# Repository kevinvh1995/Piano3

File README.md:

# VHDL Piano Project

This project involves designing and implementing a functional digital piano on a Terasic DE10-Lite FPGA board using VHDL. The piano will read key presses from a PS/2 keyboard, generate corresponding musical tones, and display information on 7-segment displays. The design follows a modular, structural VHDL approach.

## Project Setup

* **Hardware:** Terasic DE10-Lite Board
* **Software:** Intel Quartus Prime Lite Edition
* **Language:** VHDL-2008
* **Target OS:** Windows
* **Shell:** powershell.exe

### Setup Steps

1. Ensure Intel Quartus Prime is installed.
2. Connect the DE10-Lite board to the PC via USB.
3. Connect a PS/2 keyboard to the GPIO pins using the appropriate interface shield.
4. Open the Quartus project file (`.qpf`) for the current assignment.
5. Compile the VHDL code and program the FPGA.

## Repository Structure Analysis

The repository contains a complete VHDL piano implementation with the following structure:

### Assignment Directories

* **assignment_0**: 7-segment decoder (`seg7dec`) - foundational component

* **assignment_1**: PS/2 serial-to-parallel converter (`showkey`)
* **assignment_2_constantKey**: Key state FSM (`constantkey`)
* **assignment_2_readKey**: Complete keyboard interface (`readkey`)
* **assignment_3**: Clock generator with octave control (`clock_generator`)
* **assignment_4**: Key-to-frequency mapping (`key2pulselength`)
* **assignment_5**: Audio tone generator (`pulselength2audio`)
* **assignment_6**: Integrated tone generation (`tone_generation`)
* **assignment_7**: Top-level piano integration (`piano`)

### Documentation

* **docs/assignment_2_211.md**: Latest assignment specification (v211)

* **docs/requirements.md**: Detailed grading criteria and requirements
* **docs/Course_manual_summary.md**: Complete course overview
* **docs/lesson_summary/**: Weekly lesson notes covering VHDL concepts
* **docs/pedroni_circuit_design/**: Reference material from textbook

### Hardware

* **hardware/**: PS/2 keyboard shield design files (Eagle & KiCad)

* **hardware/images/**: Shield photos and board layouts

## Progress Tracker

### To-Do

#### Phase 1: Component Verification & Testing

* [ ] **Assignment 0 - seg7dec Verification**
  * [ ] Open Quartus project `assignment_0/seg7dec.qpf`
  * [ ] Compile and verify synthesis without errors/warnings
  * [ ] Test all 16 input combinations (0x0-0xF) using waveform simulation
  * [ ] Verify common anode logic (0=on, 1=off) for all segments
  * [ ] Document any issues and validate against truth table
  * [ ] Test on hardware with switches if available

* [ ] **Assignment 1 - showkey Verification**
  * [ ] Open Quartus project `assignment_1/showkey.qpf`
  * [ ] Analyze PS/2 protocol implementation in `showkey.vhd`
  * [ ] Compile and resolve any synthesis issues
  * [ ] Run testbench `showkey_tb.vhd` in ModelSim
  * [ ] Verify 11-bit frame parsing (start, 8 data, parity, stop)
  * [ ] Test byte_read signal timing and scancode output
  * [ ] Validate falling edge detection of kbclock
  * [ ] Document bit counter logic and frame assembly

* [ ] **Assignment 2a - constantkey FSM Verification**
  * [ ] Open Quartus project `assignment_2_constantKey/constantkey.qpf`
  * [ ] Analyze Moore FSM implementation with 5 states
  * [ ] Verify state transition logic in RTL viewer
  * [ ] Run testbench `constantkey_tb.vhd` in ModelSim
  * [ ] Test key press/release sequence detection
  * [ ] Verify 0xF0 release code handling
  * [ ] Validate memory signals for dig2/dig3 debug outputs
  * [ ] Check for latch inference warnings

* [ ] **Assignment 2b - readkey Integration Verification**
  * [ ] Open Quartus project `assignment_2_readKey/readkey.qpf`
  * [ ] Analyze structural VHDL combining clock_domain_crossing, showkey, constantkey
  * [ ] Verify signal connections in RTL viewer
  * [ ] Run integrated testbench `readkey_tb2.vhd`
  * [ ] Test complete keyboard interface pipeline
  * [ ] Validate clock domain crossing synchronizers
  * [ ] Verify end-to-end key press to scancode output

* [ ] **Assignment 3 - clock_generator Verification**
  * [ ] Open Quartus project `assignment_3/clock_generator.qpf`
  * [ ] Analyze FSM controlling clock divider multiplexer
  * [ ] Verify 7 octave states (50MHz down to 0.78125MHz)
  * [ ] Run testbench `tb_clock_generator.vhd`
  * [ ] Test 'A' key (octave up) and 'Z' key (octave down) responses
  * [ ] Validate frequency division ratios in simulation
  * [ ] Check state machine viewer in Quartus

* [ ] **Assignment 4 - key2pulselength Verification**
  * [ ] Open Quartus project `assignment_4/key2pulselength.qpf`
  * [ ] Analyze lookup table implementation for note frequencies
  * [ ] Verify scancode to frequency divisor mapping
  * [ ] Run testbench `tb_key2pulselength.vhd`
  * [ ] Test key mappings from Table 3 (22 notes)
  * [ ] Validate integer range 0-8191 for pulselength output
  * [ ] Cross-reference with musical note frequencies

* [ ] **Assignment 5 - pulselength2audio Verification**
  * [ ] Open Quartus project `assignment_5/pulselength2audio.qpf`
  * [ ] Analyze counter-based frequency divider
  * [ ] Verify audio square wave generation logic
  * [ ] Run testbench `tb_pulselength2audio.vhd`
  * [ ] Test with various pulselength values (0, 100, 1000, 7000)
  * [ ] Measure output frequencies and validate timing
  * [ ] Verify stereo output (audiol, audior)

* [ ] **Assignment 6 - tone_generation Integration**
  * [ ] Open Quartus project `assignment_6/tone_generation.qpf`
  * [ ] Verify structural combination of clock_generator, key2pulselength, pulselength2audio
  * [ ] Run testbench `TB_tone_generation.vhd`
  * [ ] Test complete tone synthesis pipeline
  * [ ] Validate signal connections in RTL viewer
  * [ ] Verify octave shifting affects output frequency correctly

#### Phase 2: System Integration & Hardware Testing

* [ ] **Assignment 7 - Top-Level Piano Integration**
  * [ ] Open Quartus project `assignment_7/piano.qpf`
  * [ ] Analyze top-level structural VHDL connections
  * [ ] Verify pin assignments in `piano.qsf` file
  * [ ] Compile full system and resolve any errors
  * [ ] Run complete system testbench `tb_piano.vhd`
  * [ ] Validate HEX display connections (4x seg7dec instances)
  * [ ] Check Arduino shield pin mappings (io3-io5)

* [ ] **Hardware Preparation**
  * [ ] Verify DE10-Lite board availability and setup
  * [ ] Check PS/2 keyboard shield assembly
  * [ ] Test PS/2 keyboard with shield connection
  * [ ] Verify speaker output on shield
  * [ ] Program FPGA with compiled piano.sof file

* [ ] **System Validation & Testing**
  * [ ] Test reset functionality (KEY1, LED0 indicator)
  * [ ] Verify 7-segment displays show scancode values
  * [ ] Test all mapped piano keys for audio output:
    * [ ] QWERTY row (white keys): Q,W,E,R,T,Y,U,I,O,P
    * [ ] Number row (black keys): 1,2,3,4,5,6,7,8,9,0
  * [ ] Test octave controls:
    * [ ] 'A' key increases octave (higher pitch)
    * [ ] 'Z' key decreases octave (lower pitch)
  * [ ] Validate audio frequencies match expected musical notes
  * [ ] Test key press/release state management
  * [ ] Record demonstration video for submission

#### Phase 3: Code Quality & Documentation

* [ ] **VHDL Code Review & Standards Compliance**
  * [ ] Verify all reserved words use CAPITALS
  * [ ] Check consistent indentation across all files
  * [ ] Validate meaningful signal and variable names
  * [ ] Ensure proper use of CONSTANT declarations
  * [ ] Verify no BUFFER ports are used
  * [ ] Check TYPE definitions for all FSM states
  * [ ] Validate rising_edge(clk) usage over clk'EVENT
  * [ ] Review sensitivity lists for completeness
  * [ ] Check for latch inference warnings

* [ ] **Documentation & Comments Enhancement**
  * [ ] Update file headers with student information
  * [ ] Add comprehensive component documentation
  * [ ] Document all signal purposes and connections
  * [ ] Create architecture diagrams for complex components
  * [ ] Add timing diagrams for critical interfaces
  * [ ] Document design decisions and trade-offs

* [ ] **Testbench Validation & Coverage**
  * [ ] Ensure all components have working testbenches
  * [ ] Validate test coverage for edge cases
  * [ ] Add assertions for automatic verification
  * [ ] Document expected vs actual results
  * [ ] Create waveform screenshots for key tests
  * [ ] Verify ModelSim integration and wave files

#### Phase 4: Final Integration & Submission

* [ ] **Project Packaging & Git Management**
  * [ ] Create clean Git repository with proper structure
  * [ ] Add comprehensive README with setup instructions
  * [ ] Include pin assignment files and constraints
  * [ ] Package hardware test procedures
  * [ ] Create project release with ZIP archive
  * [ ] Validate all files compile without external dependencies

* [ ] **Performance Optimization & Analysis**
  * [ ] Review RTL viewer for optimal hardware utilization
  * [ ] Check timing analysis and slack margins
  * [ ] Optimize critical path delays if needed
  * [ ] Validate resource usage (LUTs, registers, RAM)
  * [ ] Document any performance bottlenecks

* [ ] **Final System Validation**
  * [ ] Perform complete end-to-end system test
  * [ ] Validate all functional requirements
  * [ ] Test edge cases and error conditions
  * [ ] Verify robust operation under various conditions
  * [ ] Create final demonstration video
  * [ ] Prepare oral presentation materials

### In-Progress

* [x] Repository analysis and documentation (COMPLETED)

* [x] Understanding project architecture and dependencies (COMPLETED)
* [x] Technical requirements identification (COMPLETED)
* [ ] Component-by-component verification starting with Assignment 0

### Done

* [x] Complete repository structure analysis

* [x] Documentation review and synthesis of all course materials
* [x] Technical requirements identification and grading criteria understanding
* [x] VHDL code analysis of key components (seg7dec, showkey, constantkey, piano)
* [x] Architecture mapping and component dependency analysis
* [x] README.md comprehensive documentation update
* [x] Progress tracker framework establishment with extensive task breakdown

## Architecture Overview

The VHDL piano consists of two main subsystems:

### 1. Keyboard Interface (`readKey`)

* **Clock Domain Crossing**: Synchronizes PS/2 signals (20kHz) to FPGA clock (50MHz)

* **Serial Decoder (`showkey`)**: Converts 11-bit PS/2 frames to 8-bit scancodes
* **State Machine (`constantkey`)**: Manages key press/release events and hold states

### 2. Tone Generation (`tone_generation`)

* **Clock Generator**: FSM-controlled frequency divider for octave selection

* **Key Mapper**: Lookup table converting scancodes to frequency divisors
* **Audio Generator**: Variable-frequency square wave generator

### 3. User Interface

* **7-Segment Displays**: Debug output showing current/previous key scancodes

* **Audio Output**: Square wave tones through Arduino shield speaker
* **Control**: Reset via KEY1, octave control via 'A'/'Z' keys

## Key Technical Concepts Implemented

### VHDL Design Patterns

* **Structural VHDL**: Hierarchical component instantiation

* **Moore FSMs**: State machines with output dependent only on current state
* **Clock Domain Crossing**: Two-flip-flop synchronizers for metastability prevention
* **Concurrent vs Sequential**: Proper use of processes vs concurrent statements

### Hardware Concepts

* **PS/2 Protocol**: 11-bit serial frames with clock/data handshaking

* **Audio Generation**: Digital frequency synthesis using counters
* **7-Segment Displays**: Common anode display driving with lookup tables

## Design Notes & Rationale

### Architecture Decisions

* All finite state machines use Moore machine architecture for predictable outputs

* Clock domain crossing properly handled with two-flip-flop synchronizers
* Signal naming follows consistent conventions (e.g., `C_` prefix for internal signals)
* Constants used for all magic numbers and configuration values
* Structural VHDL used for clear hierarchical design

### VHDL Best Practices Observed

* **Code Style**: CAPITALS for reserved words, consistent indentation

* **Language Usage**: `CONSTANT`s instead of magic numbers, avoid `BUFFER` ports
* **FSM Implementation**: `TYPE` definitions for state names, proper sensitivity lists
* **Edge Detection**: `rising_edge(clk)` preferred over `clk'EVENT AND clk='1'`
* **Testbenches**: Comprehensive verification for each component

### Frequency Calculation

Musical notes follow the equal temperament scale where each semitone is 2^(1/12) ≈ 1.05946 times the previous.
Base frequency: A4 = 440 Hz
Octave relationship: A5 = 880 Hz (2 × A4)

## Component Dependencies

```
piano (top-level)
├── readkey
│   ├── clock_domain_crossing
│   ├── showkey  
│   └── constantkey
├── tone_generation
│   ├── clock_generator
│   ├── key2pulselength
│   └── pulselength2audio
└── seg7dec (×4 instances)
```

## Key Requirements Summary

### Functional Requirements

* Generate correct musical tones for mapped keys (QWERTY row = white keys, number row = black keys)

* Octave changes with 'A' (up) and 'Z' (down) keys  
* Display current and previous key scancodes on HEX displays
* Reset functionality via KEY1 with LED0 status indication

### Technical Requirements

* **Code Style**: Use CAPITALs for reserved words, consistent indentation, meaningful comments

* **VHDL Usage**: Use `CONSTANT`s, avoid `BUFFER` ports, use `TYPE` for FSM states, use `rising_edge(clk)`
* **Architecture**: Modular structural VHDL design with Moore machine FSMs
* **Verification**: Testbenches for all components, simulation-based validation

### Grading Criteria (70% Code + 30% Oral)

* **Code Style** (20%): Formatting, comments, documentation

* **VHDL Language Usage** (30%): Proper constructs, no latches, good FSM design
* **Functionality** (50%): Working audio, octave control, displays, reset

## Courses

This library is used in the following coures:

* D-H-ESE-SOC

Please contact the lecturer of your course when the course you attend is not mentioned here.

# PS/2 interface shield

The hardware for the [PS/2 interface shield](hardware/README.md) is available.

## Disclaimer

Project templates and materials for the VHDL ALU assignment in SOC class is distributed in the hope that it will be useful, but WITHOUT ANY WARRANTY; Without even the implied warranty of MERCHANTABILITY or FITNESS FOR A PARTICULAR PURPOSE.

## License

VHDL examples for use in SOC class are free: You can redistribute it and/or modify it under the terms of a Creative Commons Attribution-NonCommercial 4.0 International License (<http://creativecommons.org/licenses/by-nc/4.0/>) by Remko Welling (<https://ese.han.nl/~rwelling/>) E-mail: <remko.welling@han.nl>.

<br />This work is licensed under a <a rel="license" href="http://creativecommons.org/licenses/by-nc/4.0/">Creative Commons Attribution-NonCommercial 4.0 International License</a>.

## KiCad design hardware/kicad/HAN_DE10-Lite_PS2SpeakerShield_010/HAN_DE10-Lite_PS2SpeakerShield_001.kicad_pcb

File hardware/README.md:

# PS/2 keyboard interface shield for DE10-Lite
All information required to build your own PS/2 keyboard interface shield for DE10-Lite.

## Responsible disclosure 
Students and lecturers are encouraged to send in their experiences, problems, errors, any other observation while using this document or the PS/2 keyboard interface shield for DE10-Lite. Please send your feedback to one of the lecturers, by raising an issue with this repository, so we can improve this paper. Thank you.

More about responsible disclosure, see: https://en.wikipedia.org/wiki/Responsible_disclosure 

## Disclaimer
The PS/2 keyboard interface shield for DE10-Lite is provided in the hope that it will be useful, but WITHOUT ANY WARRANTY; without even the implied warranty of MERCHANTABILITY or FITNESS FOR A PARTICULAR PURPOSE.
  
## License
The PS/2 keyboard interface shield for DE10-Lite is part of the SOC classes for HAN Engineering Hoofdmodule Embedded Hardware Engineering.

The design of the PS/2 keyboard interface shield for DE10-Lite is free: You may redistribute it and/or modify it under the terms of a Creative  Commons Attribution-NonCommercial 4.0 International License (http://creativecommons.org/licenses/by-nc/4.0/).

<br />This work is licensed under a <a rel="license" href="http://creativecommons.org/licenses/by-nc/4.0/">Creative Commons Attribution-NonCommercial 4.0 International License</a>.

# About this documentation
In the System On Chip Classes of the University of Applied sciences of Arnhem and Nijmegen (HAN) one assignment is used to introduce the students to the use of sequential VHDL code. The assignment is constructing a electronic piano using VHDL on a DE10-Lite FPGA prototype board. 

Where some predecessors of the DE10-lite board were equipped with a PS/2 female connector, the DE10-Lite is equipped with Arduino shield compatible connectors but not the PS/2 connector. This complicates the connection of a PS/2 keyboard to the DE10-Lite significantly. Therefore a interface board was developed that will use the Arduino shield factor connectors and piggy-back on the DE10-Lite board.

[Full size picture of Shield on DE10-Lite board](images/PS2SpeakerShieldOnDE10-Lite_small.png)

# Design
The purpose of the PS/2 keyboard interface shield to add neccessary electronics and make the levelchanges from 5V TTL to the 3,3V domain to guard the FPGA from damage.

The PS/2 keyboard interface shield is designed with reproduction in mind. Component selection was made to allow a introduction to working with SMD components an doldering of those. Therefore 1206 sized components are used in the design to introduce to SMD and regular trough-hole components.

The shield delivers:
 - PS/2 compatible interface to the FPGA on the DE10-Lite board. Any PS/2 compatible keyboard can be connected to the shield.
 - Loudspeaker to make tones of the VHDL-piano audible.
 
### USB-keyboards
As PS/2 is depreciated, modern keyboards have a USB connector. It was out of scope to develop a USB interface for the DE10-Lite board but from experince it was found that simple USB to PS/2 adapters work fine.

## Schematic
The electronics design for the shield is copied from the DE0-CV FPGA board schematics. Follow this link to view or download the [full size schematic](images/PS2SpeakerShield.png)

The [Eagle schematic file ](eagle/HAN_DE10-Lite_PS2SpeakerShield_001.sch) is available for download.

## PCB design
The [Eagle board file ](eagle/HAN_DE10-Lite_PS2SpeakerShield_001.brd) is available for download.

## Component layout
For soldering the component layout is made availabale separately. Click on "[Full size component layout](images/PS2SpeakerShield_BoardTopView.png)" to view or download the component layout. 

# Ordering
For PCB ordering and delivery in Europe, Aisler is recommended: https://aisler.net/ where you can directly order the board following this link: https://aisler.net/p/FWVGCYFB

## BOM
The Bill of Materials (BOM) contains easy obtainable components that can be purchased online:
```
Part Value   Package            Description
C1   100n    C1206              CAPACITOR
C2   100n    C1206              CAPACITOR
C3   100n    C1206              CAPACITOR
C4   100n    C1206              CAPACITOR
D1   BAT54S  SOT23              Schottky barrier (double)
D2   BAT54S  SOT23              Schottky barrier (double)
D3   BAT54S  SOT23              Schottky barrier (double)
D4   BAT54S  SOT23              Schottky barrier (double)
R1   2K      M1206              RESISTOR
R2   2K      M1206              RESISTOR
R3   2K      M1206              RESISTOR
R4   2K      M1206              RESISTOR
R5   200     M1206              RESISTOR
R6   200     M1206              RESISTOR
R7   200     M1206              RESISTOR
R8   200     M1206              RESISTOR
R9   200     M1206              RESISTOR
X1   DIN6FE  M_DIN6             6-PIN MINI-DIN female connector
LS1  SPEAKER PCB_MOUNT_SPEAKER  Speaker
```

# Soldering the PS/2 keyboard shield
Soldering the PS/2 keyboard interface shield kit is fun!

 - For those who start with soldering, Sparkfun hase a nice how-to availabale: https://learn.sparkfun.com/tutorials/how-to-solder-through-hole-soldering/
 - For soldering SMD components the instructions of David Haillant are recommended: http://www.davidhaillant.com/smd-soldering/
 
In this (Dutch) instruction we are soldering SMD 1206 components on the PS/2 keyboard interface PCB.

## Recommended order
When soldering the recommended order is to work "from small to big".

 1. Start with soldering the SMD resisitors
 2. Than solder the SMD capacitors
 3. Finalize soldering SMD components with the diodes
 4. Solder the loadspeaker
 5. Solder the PS/2 connector
 6. Cut the pin-headers to the reqired length
 6. Solder the pin-headers

# Testing

To test the PS/2 keyboard interface shield use the Quartus project that is provided with this repository: [Hardware test for PS/2 interface shield for DE10-Lite](harwareTest/README.md)

# Conclusion
Soldering is fun! I hope you enjoy your self-made PS/2 keyboard interface shield and the joy of playing your VHDL piano.

# Errata
Date      | Issue
----------|-------------
25-3-2021:| Resistors R5 to R9 have been replaced by 200 ohm.

# Hacks
Some hacks are possible to the board:

## Increase speaker audio.
The loudspeaker audio is attennuated using R9. To increase audio volume replace R9 with 0 ohm (bridge).

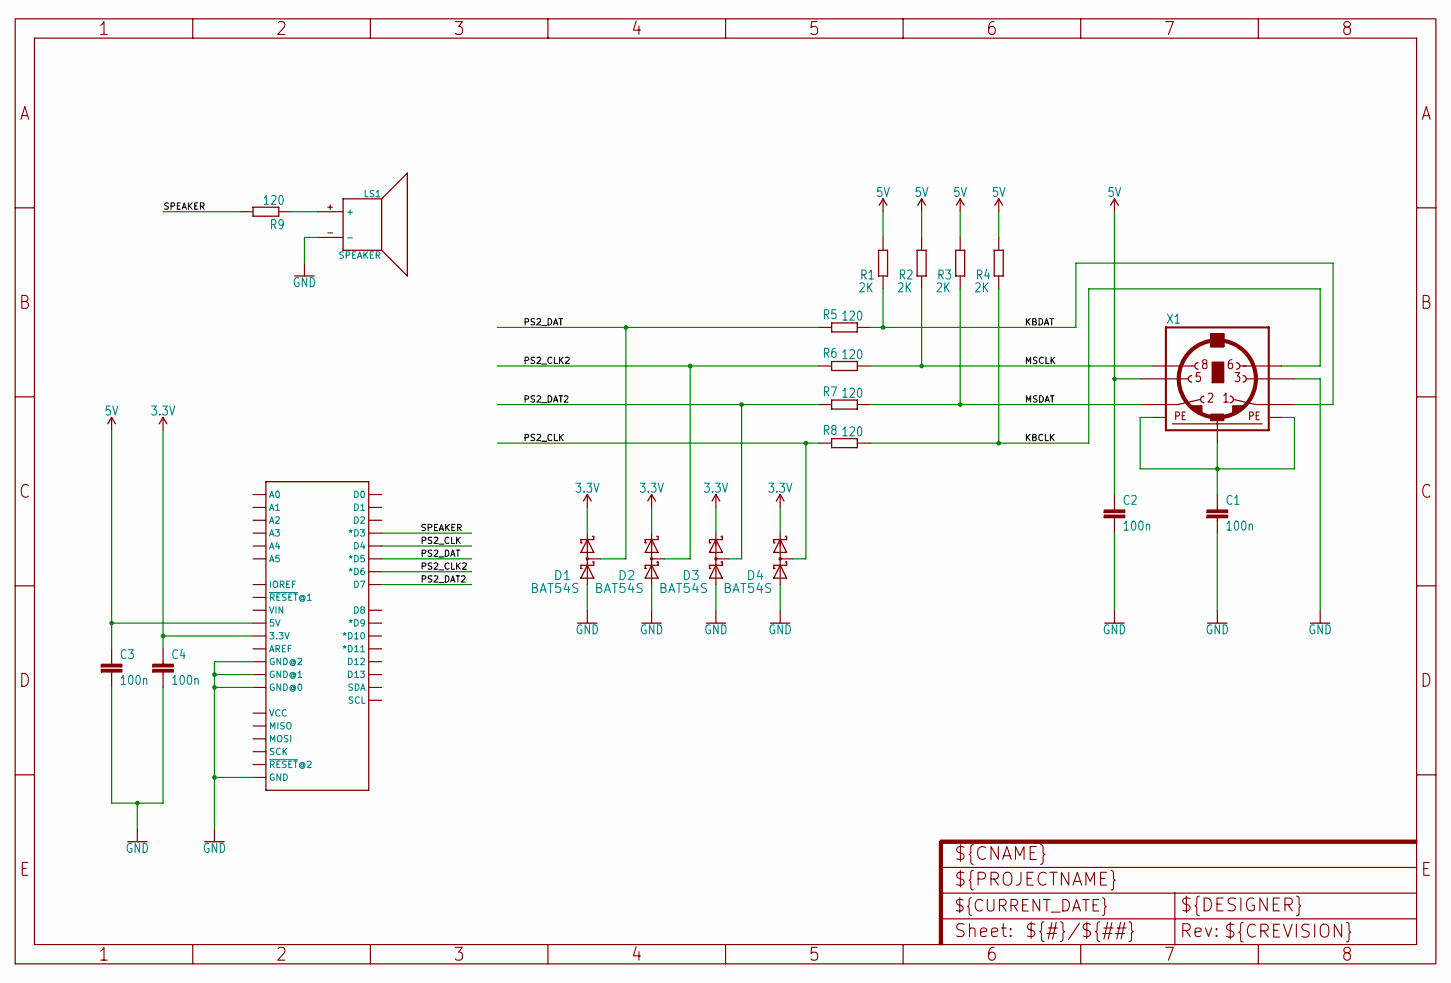
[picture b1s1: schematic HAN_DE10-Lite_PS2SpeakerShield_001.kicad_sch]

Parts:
B1: ARDUINO_UNO_R3_SHIELD_ICSP; UNO_R3_SHIELD_ICSP
C1, C2, C3, C4: 100n; C1206
D1, D2, D3, D4: BAT54S; SOT23
LS1: SPEAKER; PCB_MOUNT_SPEAKER
R1, R2, R3, R4: 2K; M1206
R5, R6, R7, R8, R9: 120; M1206
X1: MINI_DIN_6; M_DIN6

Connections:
3.3V: B1.3.3V, C4.1, D1.2 (K2), D2.2 (K2), D3.2 (K2), D4.2 (K2)
5V: B1.5V, C2.1, C3.1, R1.2, R2.2, R3.2, R4.2, X1.5
GND: B1.GND@0, B1.GND@1, B1.GND@2, B1.GND_ICSP (GND), C1.2, C2.2, C3.2, C4.2, D1.1 (A1), D2.1 (A1), D3.1 (A1), D4.1 (A1), LS1.-, X1.3
KBCLK: R4.1, R8.1, X1.6
KBDAT: R1.1, R5.1, X1.1
MSCLK: R2.1, R6.1, X1.8
MSDAT: R3.1, R7.1, X1.2
unnamed: LS1.+, R9.1
unnamed: C1.1, X1.SH1 (PE1), X1.SH2 (PE2), X1.SH3 (PE3)
PS2_CLK: B1.D4, D4.3 (K1A2), R8.2
PS2_CLK2: B1.D6 (*D6), D2.3 (K1A2), R6.2
PS2_DAT: B1.D5 (*D5), D1.3 (K1A2), R5.2
PS2_DAT2: B1.D7, D3.3 (K1A2), R7.2
SPEAKER: B1.D3 (*D3), R9.2

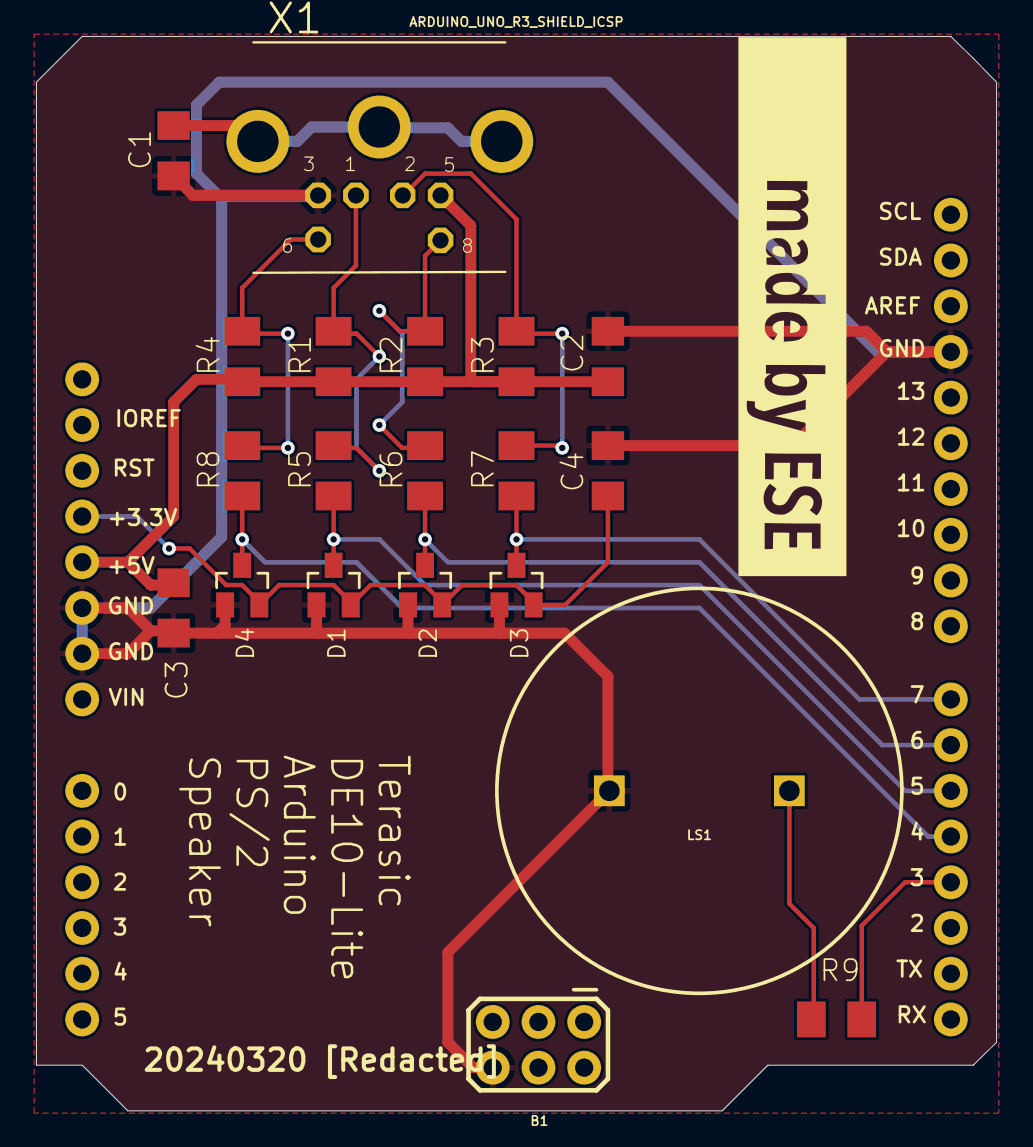
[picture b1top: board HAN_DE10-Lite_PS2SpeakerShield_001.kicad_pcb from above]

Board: 2 copper layers, 53.3 x 59.7 mm, 20 parts (0 on the bottom side), 14 nets.

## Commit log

2020-03-21 Added board an assignment 4
2020-03-22 Added templates for assignments 1 and 2
2020-03-31 Added exercise 0 1 and b
2020-04-01 Added FSM example
2020-04-03 Updated assignment_2, split in to two parts according to manual.
2020-04-06 Added example clock divider
2020-04-07 Added assignment 3 and 4
2020-04-07 Added top-level Entity piano.vhd
2020-04-09 Simplified assignment 0, renamed a to 0 and removed b
2020-05-04 Changed naming states
2020-05-13 Update hardware documentation
2020-05-13 Added readme.md to hardware
2020-05-13 Another update
2020-05-14 Updated shield documentation
2020-05-14 Final addition to hardware/README.md
2020-05-14 Duh, always something you forget
2020-05-14 Mopper
2020-05-15 Added test project for testing PS/2 keyboard interface shield
2020-05-15 Sigh
2020-05-18 added start to send data to keyboard test
2020-05-18 Added first file
2020-05-25 Corrected tb_clock_generator.vhd of assignment_3. Courtesey of Wesley Oldenburg
2020-05-26 Added assignment_5/pulselength2audio.vhd because of missing. Courtesy of Maurice Maters
2020-05-29 Added instruction video for SMD 1206
2020-06-05 Modified documentation
2020-07-06 Updated comment on updating headers
2020-12-30 Updated student information
2021-03-25 Added Errata and Hacks for hardware.
2021-03-25 Added direct link to Aisler for ordering the board
2021-05-25 Updated files and corrected test bench and added instruction
2021-05-25 Correction
2022-03-02 Added possibility for students to add names to files they worked on.
2022-04-05 Update README.md, added course reference.
2022-05-30 Corrected documentation
2024-03-20 Initial commit after Eagle import in to Kicad
2024-03-20 Updated documentation
2024-05-15 Some additions
2025-05-06 Added 7out4 display driver from assignment 0
2025-05-06 Initial version of showkey
2025-05-06 Generated testbench
2025-05-06 Added code snippet 8 to the testbench
2025-05-09 assignment 00
2025-06-20 added files
2025-06-20 Names
2025-06-21 Added decoder
2025-06-21 Remove PII from various project files
    Removed names, email addresses, student numbers, and initials from README.md, .vhd, and .kicad_pcb files throughout the repository to protect personal information.
2025-06-21 doc: Restructure project with comprehensive documentation and remove PDFs
    - Create extensive course documentation including lesson summaries and assignments
    - Add Pedroni circuit design documentation (10 chapters)
    - Update README with new project structure and requirements
